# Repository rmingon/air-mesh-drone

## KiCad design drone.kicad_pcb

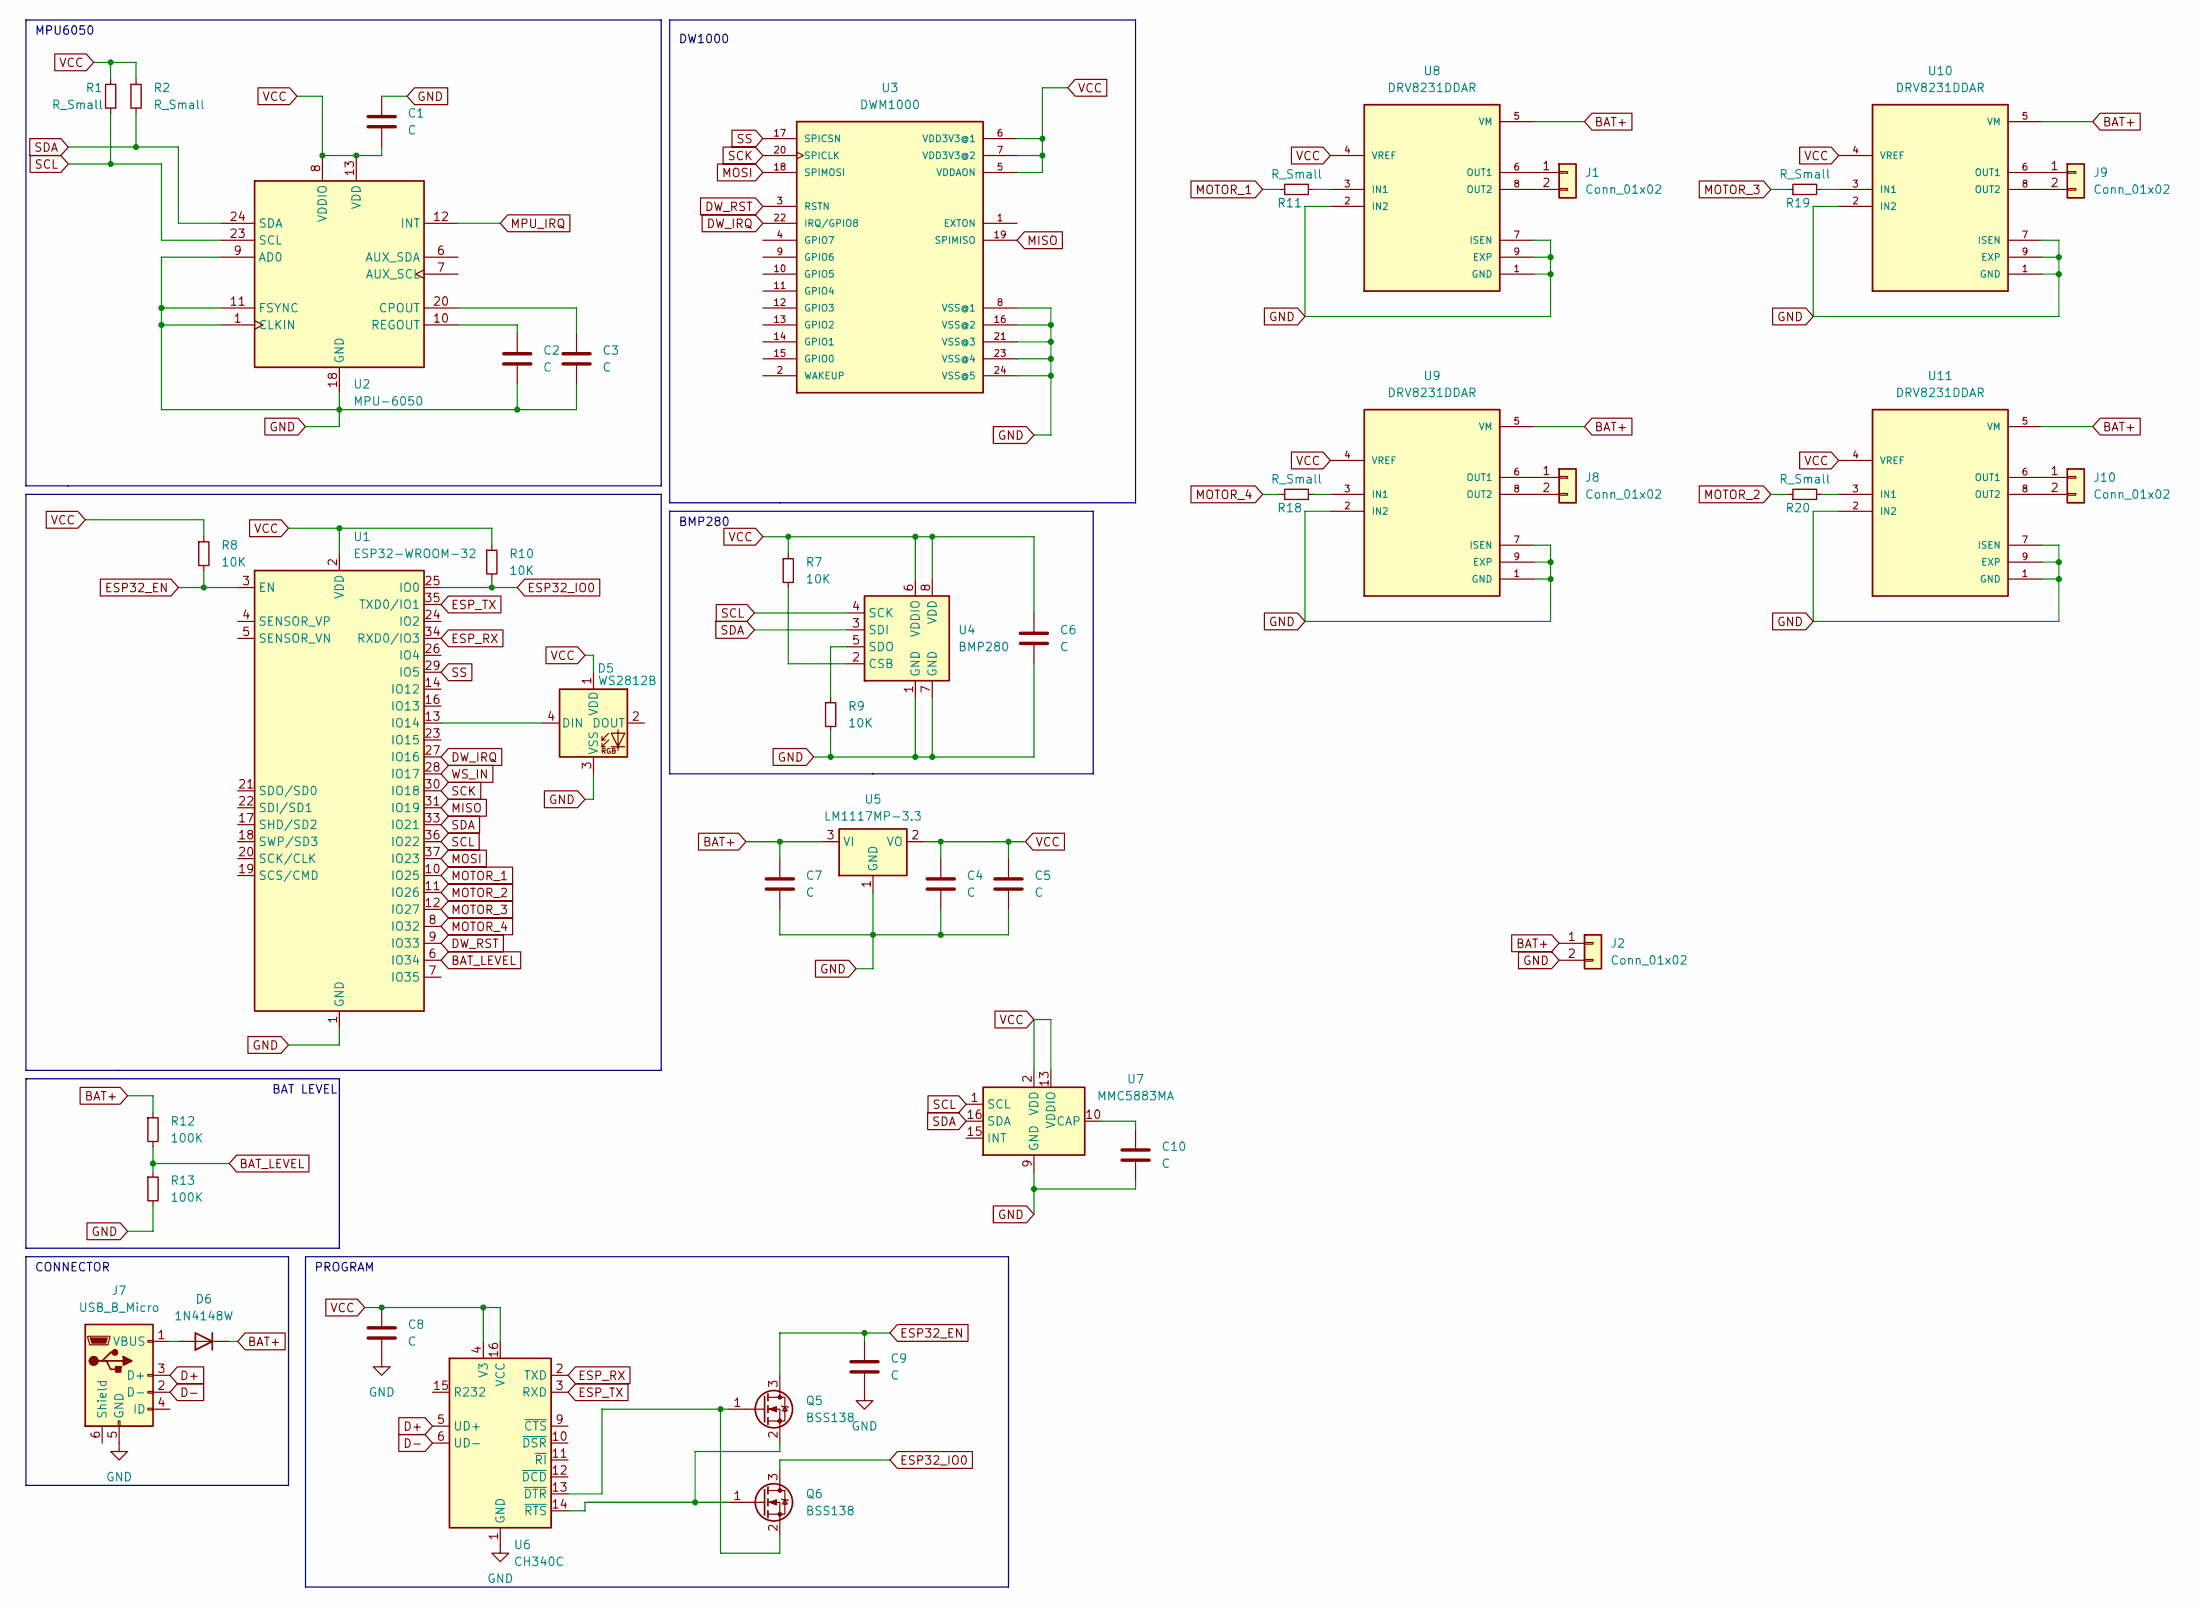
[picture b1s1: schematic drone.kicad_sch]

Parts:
C1, C2, C3, C4, C5, C6, C7, C8, C9, C10: C; C_0603_1608Metric
D5: WS2812B; LED_WS2812B_PLCC4_5.0x5.0mm_P3.2mm
D6: 1N4148W; D_SOD-123
J1, J8, J9, J10: Conn_01x02; PinHeader_1x02_P2.54mm_Vertical
J2: Conn_01x02; AMASS_XT30U-F_1x02_P5.0mm_Vertical
J7: USB_B_Micro; USB_Micro-B_Amphenol_10118194_Horizontal
Q5, Q6: BSS138; SOT-23
R1, R2, R11, R18, R19, R20: R_Small; R_0603_1608Metric
R7, R8, R9, R10: 10K; R_0603_1608Metric
R12, R13: 100K; R_0603_1608Metric
U1: ESP32-WROOM-32
U2: MPU-6050; InvenSense_QFN-24_4x4mm_P0.5mm
U3: DWM1000
U4: BMP280; Bosch_LGA-8_2x2.5mm_P0.65mm_ClockwisePinNumbering
U5: LM1117MP-3.3; SOT-223-3_TabPin2
U6: CH340C; SOIC-16_3.9x9.9mm_P1.27mm
U7: MMC5883MA; LGA-16_3x3mm_P0.5mm
U8, U9, U10, U11: DRV8231DDAR; IC_DRV8231DDAR; PARTREV November 2021

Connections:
BAT+: C7.1, D6.1 (K), J2.1, R12.1, U5.3 (VI), U8.5 (VM), U9.5 (VM), U10.5 (VM), U11.5 (VM)
BAT_LEVEL: R12.2, R13.1, U1.6 (IO34)
D+: J7.3 (D+), U6.5 (UD+)
D-: J7.2 (D-), U6.6 (UD-)
DW_IRQ: U1.27 (IO16), U3.22 (IRQ/GPIO8)
DW_RST: U1.9 (IO33), U3.3 (RSTN)
ESP32_EN: C9.1, Q5.3 (D), R8.2, U1.3 (EN)
ESP32_IO0: Q6.3 (D), R10.2, U1.25 (IO0)
ESP_RX: U1.34 (RXD0/IO3), U6.2 (TXD)
ESP_TX: U1.35 (TXD0/IO1), U6.3 (RXD)
GND: C1.1, C2.2, C3.2, C4.2, C5.2, C6.2, C7.2, C8.2, C9.2, C10.2, D5.3 (VSS), J2.2, J7.5 (GND), R9.2, R13.2, U1.1 (GND), U1.15 (GND), U1.38 (GND), U1.39 (GND), U2.1 (CLKIN), U2.9 (AD0), U2.11 (FSYNC), U2.18 (GND), U3.8 (VSS@1), U3.16 (VSS@2), U3.21 (VSS@3), U3.23 (VSS@4), U3.24 (VSS@5), U4.1 (GND), U4.7 (GND), U5.1 (GND), U6.1 (GND), U7.9 (GND), U7.11 (GND), U8.1 (GND), U8.2 (IN2), U8.7 (ISEN), U8.9 (EXP), U9.1 (GND), U9.2 (IN2), U9.7 (ISEN), U9.9 (EXP), U10.1 (GND), U10.2 (IN2), U10.7 (ISEN), U10.9 (EXP), U11.1 (GND), U11.2 (IN2), U11.7 (ISEN), U11.9 (EXP)
MISO: U1.31 (IO19), U3.19 (SPIMISO)
MOSI: U1.37 (IO23), U3.18 (SPIMOSI)
MOTOR_1: R11.1, U1.10 (IO25)
MOTOR_2: R20.1, U1.11 (IO26)
MOTOR_3: R19.1, U1.12 (IO27)
MOTOR_4: R18.1, U1.8 (IO32)
MPU_IRQ: U2.12 (INT)
unnamed: D5.4 (DIN), U1.13 (IO14)
unnamed: D6.2 (A), J7.1 (VBUS)
unnamed: J1.1, U8.6 (OUT1)
unnamed: J1.2, U8.8 (OUT2)
unnamed: J8.1, U9.6 (OUT1)
unnamed: J8.2, U9.8 (OUT2)
unnamed: J9.1, U10.6 (OUT1)
unnamed: J9.2, U10.8 (OUT2)
unnamed: J10.1, U11.6 (OUT1)
unnamed: J10.2, U11.8 (OUT2)
unnamed: Q5.1 (G), Q6.2 (S), U6.13 (~DTR)
unnamed: Q5.2 (S), Q6.1 (G), U6.14 (~RTS)
unnamed: C3.1, U2.20 (CPOUT)
unnamed: C2.1, U2.10 (REGOUT)
unnamed: R7.2, U4.2 (CSB)
unnamed: R9.1, U4.5 (SDO)
unnamed: C10.1, U7.10 (CAP)
unnamed: R11.2, U8.3 (IN1)
unnamed: R18.2, U9.3 (IN1)
unnamed: R19.2, U10.3 (IN1)
unnamed: R20.2, U11.3 (IN1)
SCK: U1.30 (IO18), U3.20 (SPICLK)
SCL: R1.2, U1.36 (IO22), U2.23 (SCL), U4.4 (SCK), U7.1 (SCL)
SDA: R2.2, U1.33 (IO21), U2.24 (SDA), U4.3 (SDI), U7.16 (SDA)
SS: U1.29 (IO5), U3.17 (SPICSN)
VCC: C1.2, C4.1, C5.1, C6.1, C8.1, D5.1 (VDD), R1.1, R2.1, R7.1, R8.1, R10.1, U1.2 (VDD), U2.8 (VDDIO), U2.13 (VDD), U3.5 (VDDAON), U3.6 (VDD3V3@1), U3.7 (VDD3V3@2), U4.6 (VDDIO), U4.8 (VDD), U5.2 (VO), U6.4 (V3), U6.16 (VCC), U7.2 (VDD), U7.13 (VDDIO), U8.4 (VREF), U9.4 (VREF), U10.4 (VREF), U11.4 (VREF)
WS_IN: U1.28 (IO17)

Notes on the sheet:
PROGRAM
CONNECTOR
BMP280
BAT LEVEL
DW1000
MPU6050

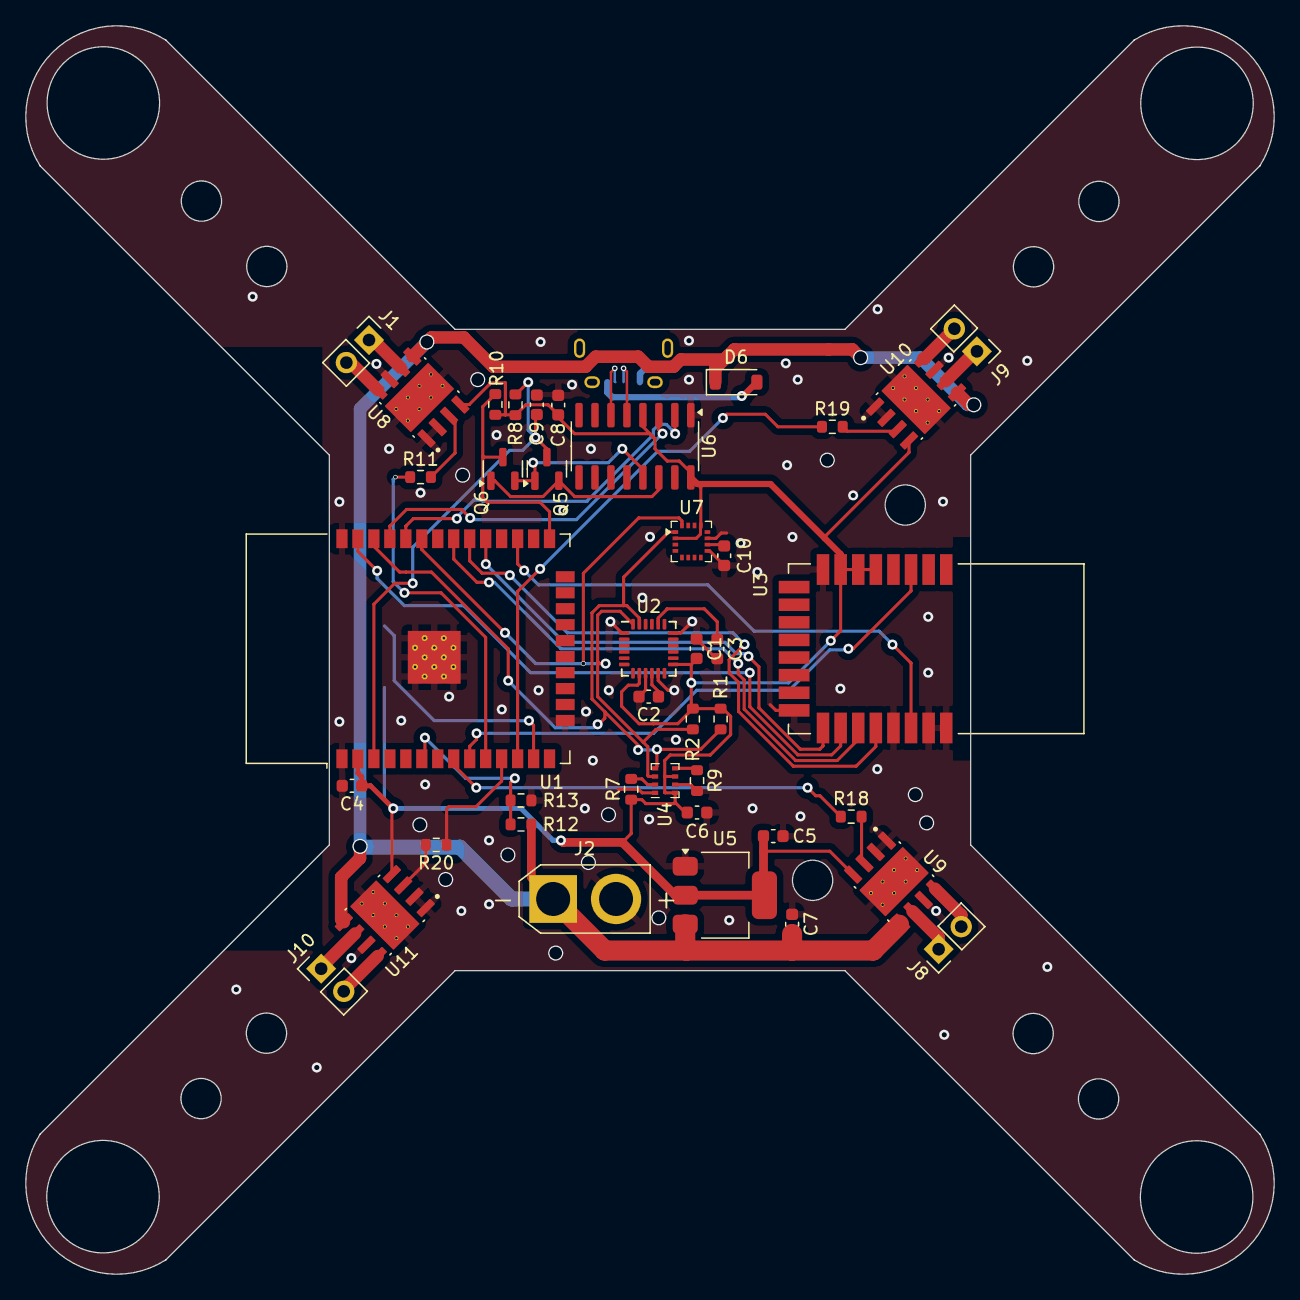
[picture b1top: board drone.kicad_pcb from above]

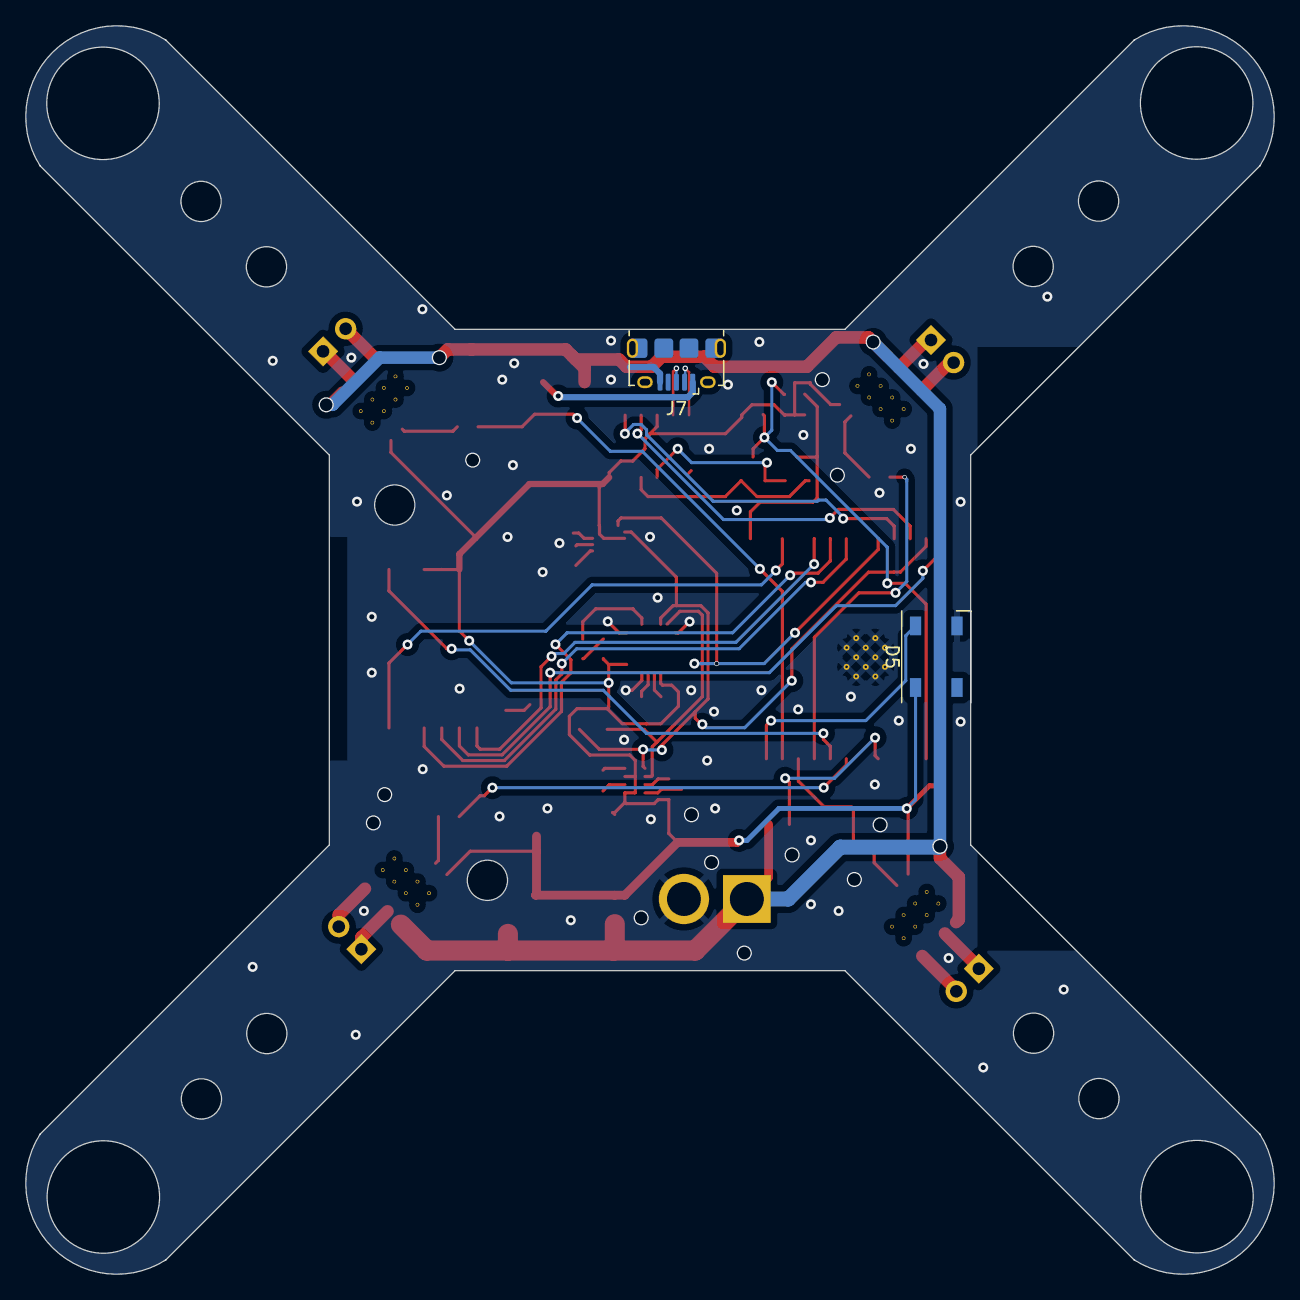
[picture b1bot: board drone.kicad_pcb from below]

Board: 2 copper layers, 99.3 x 99.3 mm, 43 parts (2 on the bottom side), 43 nets.

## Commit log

2025-03-09 bigger battery wiring
2025-03-09 add magnetometer + resive to max 10x10cm
2025-03-23 add minimal drone code
2025-03-23 add other source code
2025-04-15 pass si2301 to DRV8231
2025-04-15 pass to mpu lib to mpu light
2025-04-16 add motor driver wiring on pcb
